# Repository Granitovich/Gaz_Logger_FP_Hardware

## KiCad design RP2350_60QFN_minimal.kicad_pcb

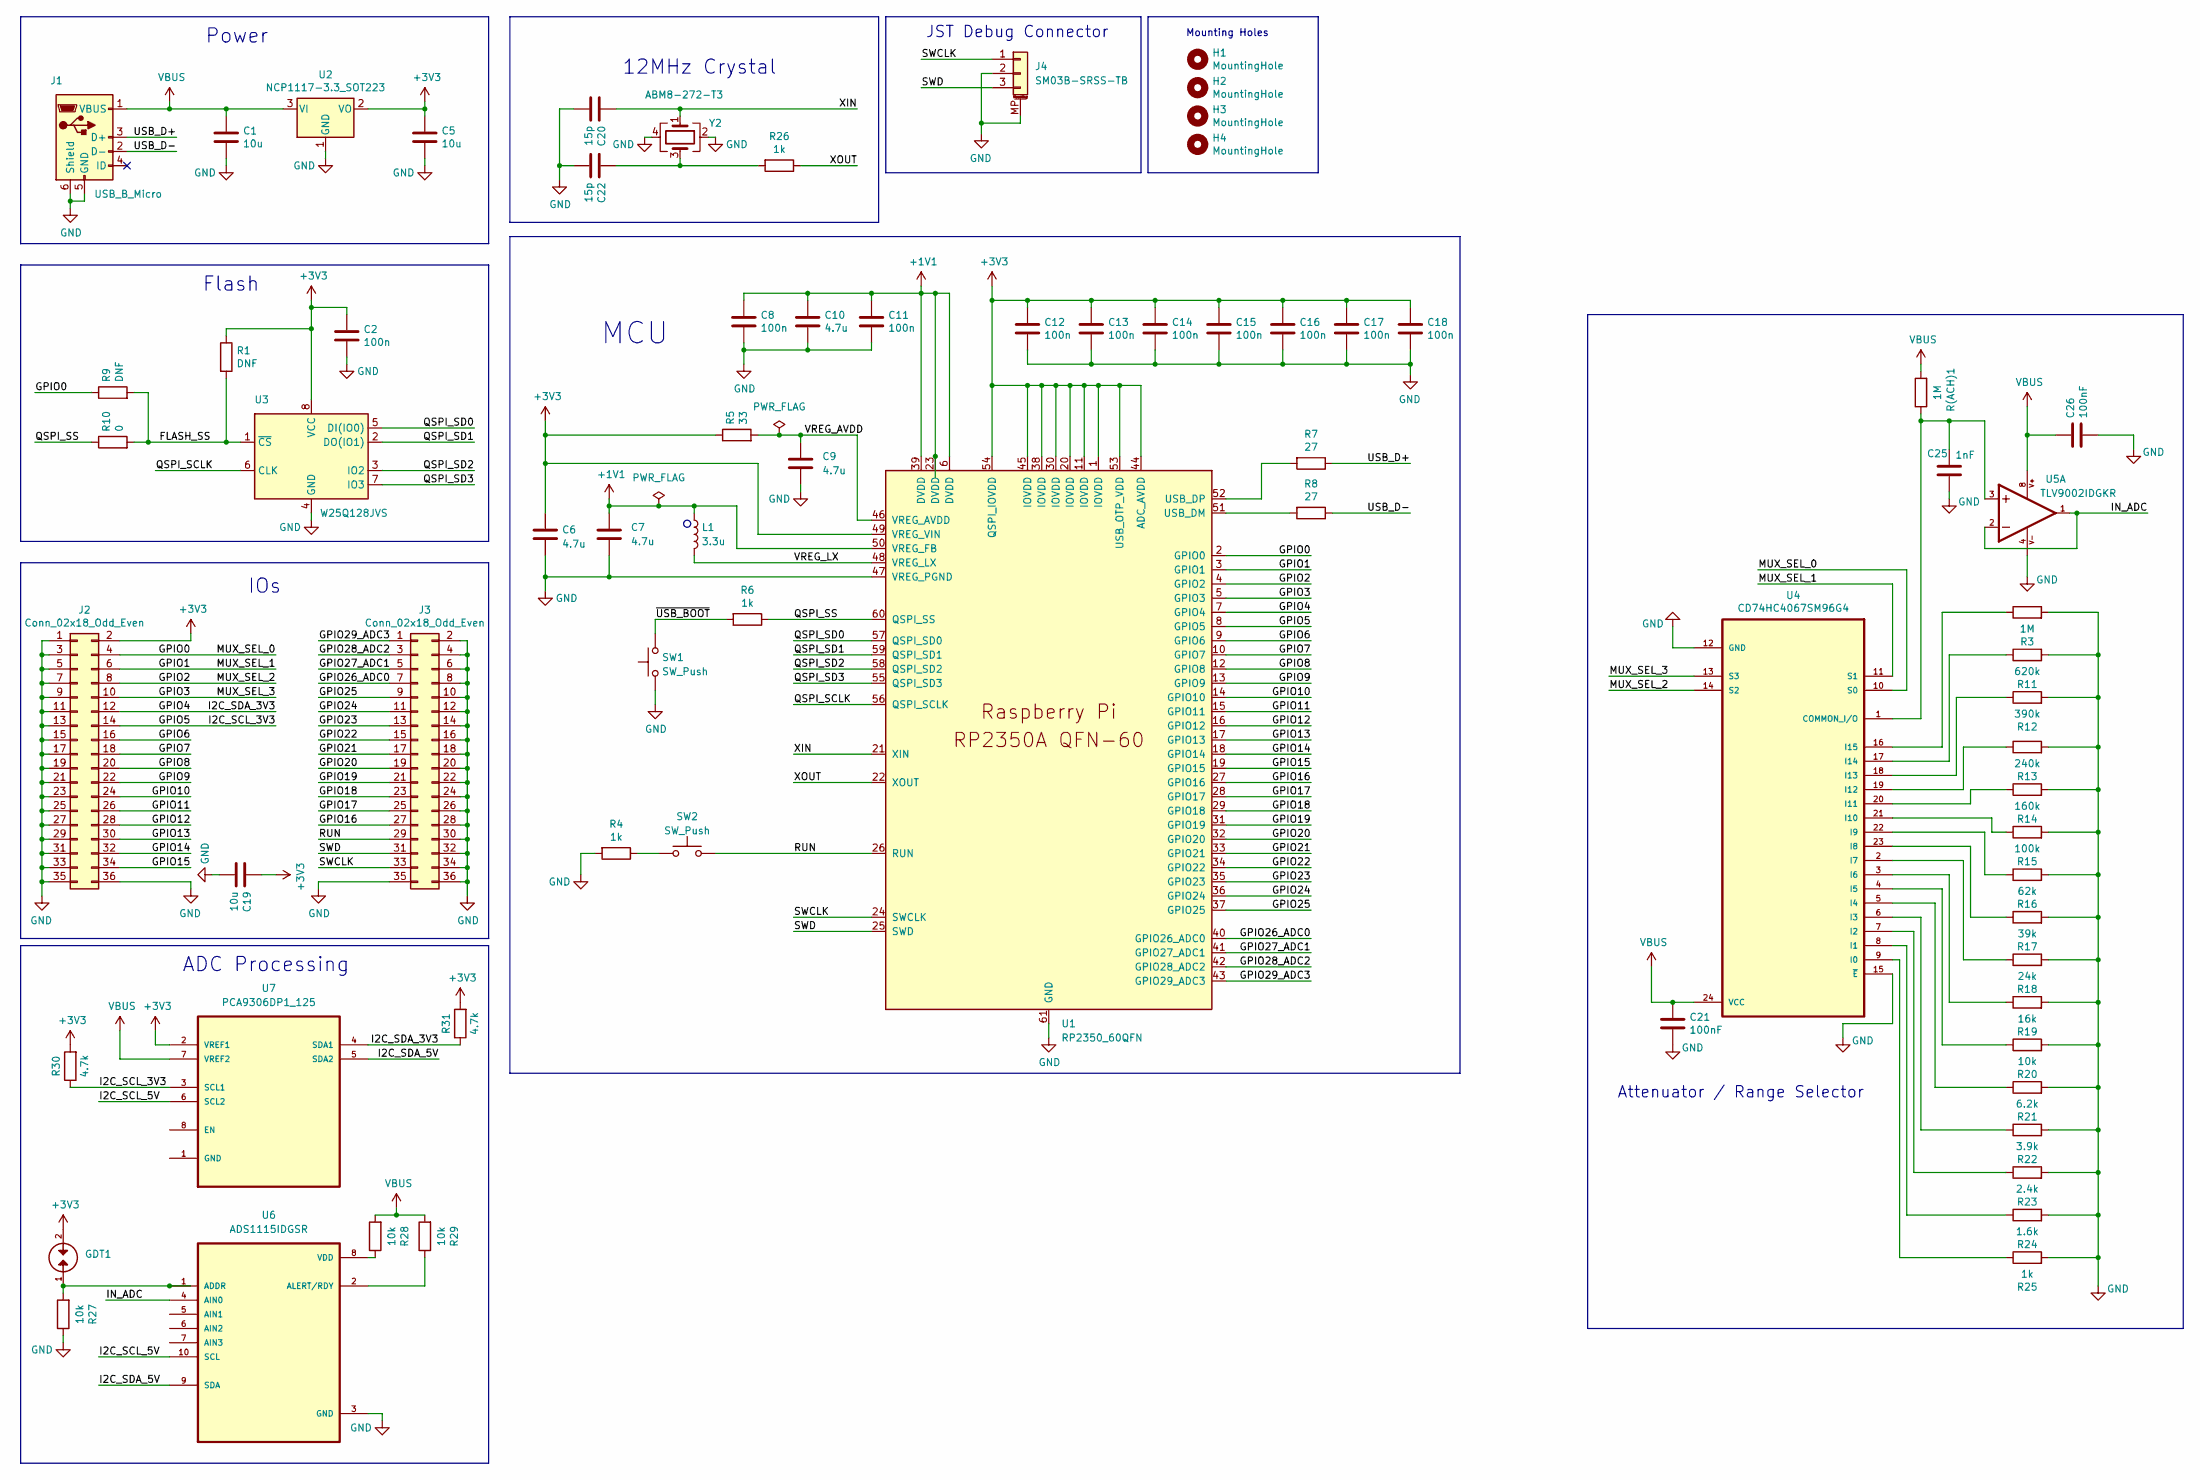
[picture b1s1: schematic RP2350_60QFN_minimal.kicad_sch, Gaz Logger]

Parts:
C1, C5, C19: 10u; C_0805_2012Metric
C2, C8, C11, C12, C13, C14, C15, C16, C17, C18: 100n; C_0402_1005Metric
C6, C7: 4.7u; C_0402_1005Metric_small_pads
C9, C10: 4.7u; C_0402_1005Metric
C20, C22: 15p; C_0402_1005Metric
C21, C26: 100nF; C_0402_1005Metric
C25: 1nF; C_0402_1005Metric
GDT1: TVS_2031-42T-SM-RPLF; PARTREV 09/17
H1, H2, H3, H4: MountingHole; MountingHole_2.7mm_M2.5
J1: USB_B_Micro; USB_Micro-B_Amphenol_10103594-0001LF_Horizontal
J2, J3: Conn_02x18_Odd_Even; PinHeader_2x18_P2.54mm_Vertical
J4: SM03B-SRSS-TB; JST_SH_SM03B-SRSS-TB_1x03-1MP_P1.00mm_Horizontal
L1: 3.3u; L_pol_2016
R1, R9: DNF; R_0402_1005Metric
R3: 1M; R_0805_2012Metric_Pad1.20x1.40mm_HandSolder
R4, R6, R26: 1k; R_0402_1005Metric
R5: 33; R_0402_1005Metric
R7, R8: 27; R_0402_1005Metric
R10: 0; R_0402_1005Metric
R11: 620k; R_0805_2012Metric_Pad1.20x1.40mm_HandSolder
R12: 390k; R_0805_2012Metric_Pad1.20x1.40mm_HandSolder
R13: 240k; R_0805_2012Metric_Pad1.20x1.40mm_HandSolder
R14: 160k; R_0805_2012Metric_Pad1.20x1.40mm_HandSolder
R15: 100k; R_0805_2012Metric_Pad1.20x1.40mm_HandSolder
R16: 62k; R_0805_2012Metric_Pad1.20x1.40mm_HandSolder
R17: 39k; R_0805_2012Metric_Pad1.20x1.40mm_HandSolder
R18: 24k; R_0805_2012Metric_Pad1.20x1.40mm_HandSolder
R19: 16k; R_0805_2012Metric_Pad1.20x1.40mm_HandSolder
R20, R27, R28, R29: 10k; R_0805_2012Metric_Pad1.20x1.40mm_HandSolder
R21: 6.2k; R_0805_2012Metric_Pad1.20x1.40mm_HandSolder
R22: 3.9k; R_0805_2012Metric_Pad1.20x1.40mm_HandSolder
R23: 2.4k; R_0805_2012Metric_Pad1.20x1.40mm_HandSolder
R24: 1.6k; R_0805_2012Metric_Pad1.20x1.40mm_HandSolder
R25: 1k; R_0805_2012Metric_Pad1.20x1.40mm_HandSolder
R30, R31: 4.7k; R_0805_2012Metric_Pad1.20x1.40mm_HandSolder
R(ACH)1: 1M; R_0805_2012Metric_Pad1.20x1.40mm_HandSolder
SW1, SW2: SW_Push; SW_Push_1P1T_NO_Vertical_Wuerth_434133025816
U1: RP2350_60QFN; RP2350-QFN-60-1EP_7x7_P0.4mm_EP3.4x3.4mm_ThermalVias
U2: NCP1117-3.3_SOT223; SOT-223-3_TabPin2
U3: W25Q128JVS; SOIC-8_5.23x5.23mm_P1.27mm
U4: CD74HC4067SM96G4; SOP65P780X200-24N
U5: TLV9002IDGKR; SOP65P490X110-8N; PARTREV L; DigiKey_Part_Number 296-50415-1-ND
U6: ADS1115IDGSR; SOP50P490X110-10N
U7: PCA9306DP1_125; SOP65P400X110-8N; MPN PCA9306DP1,125
Y2: ABM8-272-T3; Crystal_SMD_3225-4Pin_3.2x2.5mm

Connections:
+1V1: C7.1, C8.1, C10.1, C11.1, L1.1, U1.6 (DVDD), U1.23 (DVDD), U1.39 (DVDD), U1.50 (VREG_FB)
+3V3: C2.1, C5.1, C6.1, C12.1, C13.1, C14.1, C15.1, C16.1, C17.1, C18.1, C19.1, GDT1.2, J2.2, R1.1, R5.1, R30.2, R31.2, U1.1 (IOVDD), U1.11 (IOVDD), U1.20 (IOVDD), U1.30 (IOVDD), U1.38 (IOVDD), U1.44 (ADC_AVDD), U1.45 (IOVDD), U1.49 (VREG_VIN), U1.53 (USB_OTP_VDD), U1.54 (QSPI_IOVDD), U2.2 (VO), U3.8 (VCC), U7.2 (VREF1)
/FLASH_SS: R1.2, R9.2, R10.2, U3.1 (~CS)
/GPIO0: J2.4, R9.1, U1.2 (GPIO0), U4.10 (S0)
/GPIO1: J2.6, U1.3 (GPIO1), U4.11 (S1)
/GPIO2: J2.8, U1.4 (GPIO2), U4.14 (S2)
/GPIO3: J2.10, U1.5 (GPIO3), U4.13 (S3)
/GPIO4: J2.12, R31.1, U1.7 (GPIO4), U7.4 (SDA1)
/GPIO5: J2.14, R30.1, U1.8 (GPIO5), U7.3 (SCL1)
/GPIO6: J2.16, U1.9 (GPIO6)
/GPIO7: J2.18, U1.10 (GPIO7)
/GPIO8: J2.20, U1.12 (GPIO8)
/GPIO9: J2.22, U1.13 (GPIO9)
/GPIO10: J2.24, U1.14 (GPIO10)
/GPIO11: J2.26, U1.15 (GPIO11)
/GPIO12: J2.28, U1.16 (GPIO12)
/GPIO13: J2.30, U1.17 (GPIO13)
/GPIO14: J2.32, U1.18 (GPIO14)
/GPIO15: J2.34, U1.19 (GPIO15)
/GPIO16: J3.27, U1.27 (GPIO16)
/GPIO17: J3.25, U1.28 (GPIO17)
/GPIO18: J3.23, U1.29 (GPIO18)
/GPIO19: J3.21, U1.31 (GPIO19)
/GPIO20: J3.19, U1.32 (GPIO20)
/GPIO21: J3.17, U1.33 (GPIO21)
/GPIO22: J3.15, U1.34 (GPIO22)
/GPIO23: J3.13, U1.35 (GPIO23)
/GPIO24: J3.11, U1.36 (GPIO24)
/GPIO25: J3.9, U1.37 (GPIO25)
/GPIO26_ADC0: J3.7, U1.40 (GPIO26_ADC0)
/GPIO27_ADC1: J3.5, U1.41 (GPIO27_ADC1)
/GPIO28_ADC2: J3.3, U1.42 (GPIO28_ADC2)
/GPIO29_ADC3: J3.1, U1.43 (GPIO29_ADC3)
/I2C_SCL_5V: U6.10 (SCL), U7.6 (SCL2)
/I2C_SDA_5V: U6.9 (SDA), U7.5 (SDA2)
/IN_ADC: U5.1, U5.2, U6.4 (AIN0)
/QSPI_SCLK: U1.56 (QSPI_SCLK), U3.6 (CLK)
/QSPI_SD0: U1.57 (QSPI_SD0), U3.5 (DI(IO0))
/QSPI_SD1: U1.59 (QSPI_SD1), U3.2 (DO(IO1))
/QSPI_SD2: U1.58 (QSPI_SD2), U3.3 (IO2)
/QSPI_SD3: U1.55 (QSPI_SD3), U3.7 (IO3)
/QSPI_SS: R6.1, R10.1, U1.60 (QSPI_SS)
/RUN: J3.29, SW2.2, U1.26 (RUN)
/SWCLK: J3.33, J4.1, U1.24 (SWCLK)
/SWD: J3.31, J4.3, U1.25 (SWD)
/USB_D+: J1.3 (D+), R7.1
/USB_D-: J1.2 (D-), R8.1
/VREG_AVDD: C9.1, R5.2, U1.46 (VREG_AVDD)
/VREG_LX: L1.2, U1.48 (VREG_LX)
/XIN: C20.1, U1.21 (XIN), Y2.1
/XOUT: R26.1, U1.22 (XOUT)
/~USB_BOOT: R6.2, SW1.2
GND: C1.2, C2.2, C5.2, C6.2, C7.2, C8.2, C9.2, C10.2, C11.2, C12.2, C13.2, C14.2, C15.2, C16.2, C17.2, C18.2, C19.2, C20.2, C21.2, C22.2, C25.2, C26.2, J1.5 (GND), J1.6 (Shield), J2.1, J2.3, J2.5, J2.7, J2.9, J2.11, J2.13, J2.15, J2.17, J2.19, J2.21, J2.23, J2.25, J2.27, J2.29, J2.31, J2.33, J2.35, J2.36, J3.2, J3.4, J3.6, J3.8, J3.10, J3.12, J3.14, J3.16, J3.18, J3.20, J3.22, J3.24, J3.26, J3.28, J3.30, J3.32, J3.34, J3.35, J3.36, J4.2, J4.MP (MountPin), R3.2, R4.2, R11.2, R12.2, R13.2, R14.2, R15.2, R16.2, R17.2, R18.2, R19.2, R20.2, R21.2, R22.2, R23.2, R24.2, R25.2, R27.1, SW1.1, U1.47 (VREG_PGND), U1.61 (GND), U2.1 (GND), U3.4 (GND), U4.12 (GND), U4.15 (~E), U5.4, U6.3 (GND), Y2.2, Y2.4
unnamed: C22.1, R26.2, Y2.3
unnamed: R4.1, SW2.1
unnamed: R8.2, U1.51 (USB_DM)
unnamed: R7.2, U1.52 (USB_DP)
unnamed: C25.1, R(ACH)1.1, U4.1 (COMMON_I/O), U5.3
unnamed: R25.1, U4.9 (I0)
unnamed: R24.1, U4.8 (I1)
unnamed: R23.1, U4.7 (I2)
unnamed: R22.1, U4.6 (I3)
unnamed: R21.1, U4.5 (I4)
unnamed: R20.1, U4.4 (I5)
unnamed: R19.1, U4.3 (I6)
unnamed: R18.1, U4.2 (I7)
unnamed: R17.1, U4.23 (I8)
unnamed: R16.1, U4.22 (I9)
unnamed: R15.1, U4.21 (I10)
unnamed: R14.1, U4.20 (I11)
unnamed: R13.1, U4.19 (I12)
unnamed: R12.1, U4.18 (I13)
unnamed: R11.1, U4.17 (I14)
unnamed: R3.1, U4.16 (I15)
unnamed: GDT1.1, R27.2, U6.1 (ADDR)
unnamed: R29.1, U6.2 (ALERT/RDY)
unnamed: R28.1, U6.8 (VDD)
VBUS: C1.1, C21.1, C26.1, J1.1 (VBUS), R28.2, R29.2, R(ACH)1.2, U2.3 (VI), U4.24 (VCC), U5.8, U7.7 (VREF2)

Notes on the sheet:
JST Debug Connector
IOs
12MHz Crystal
ADC Processing
Flash
Attenuator / Range Selector
Mounting Holes
MCU
Power

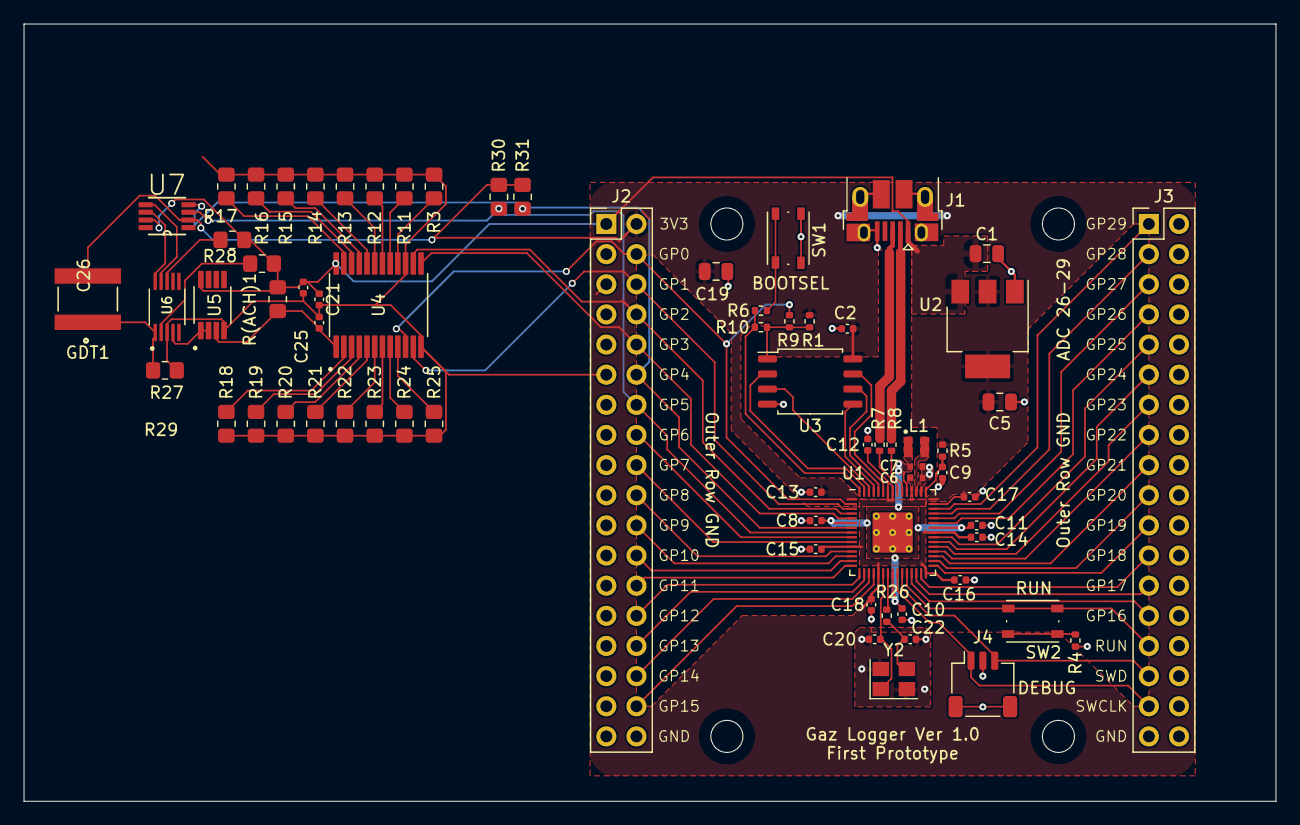
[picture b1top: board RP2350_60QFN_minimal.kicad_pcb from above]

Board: 2 copper layers, 105.5 x 65.5 mm, 73 parts (0 on the bottom side), 78 nets.
